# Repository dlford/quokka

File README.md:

## Moved to Codeberg

This project has migrated to [Codeberg](https://codeberg.org/dlford/quokka).

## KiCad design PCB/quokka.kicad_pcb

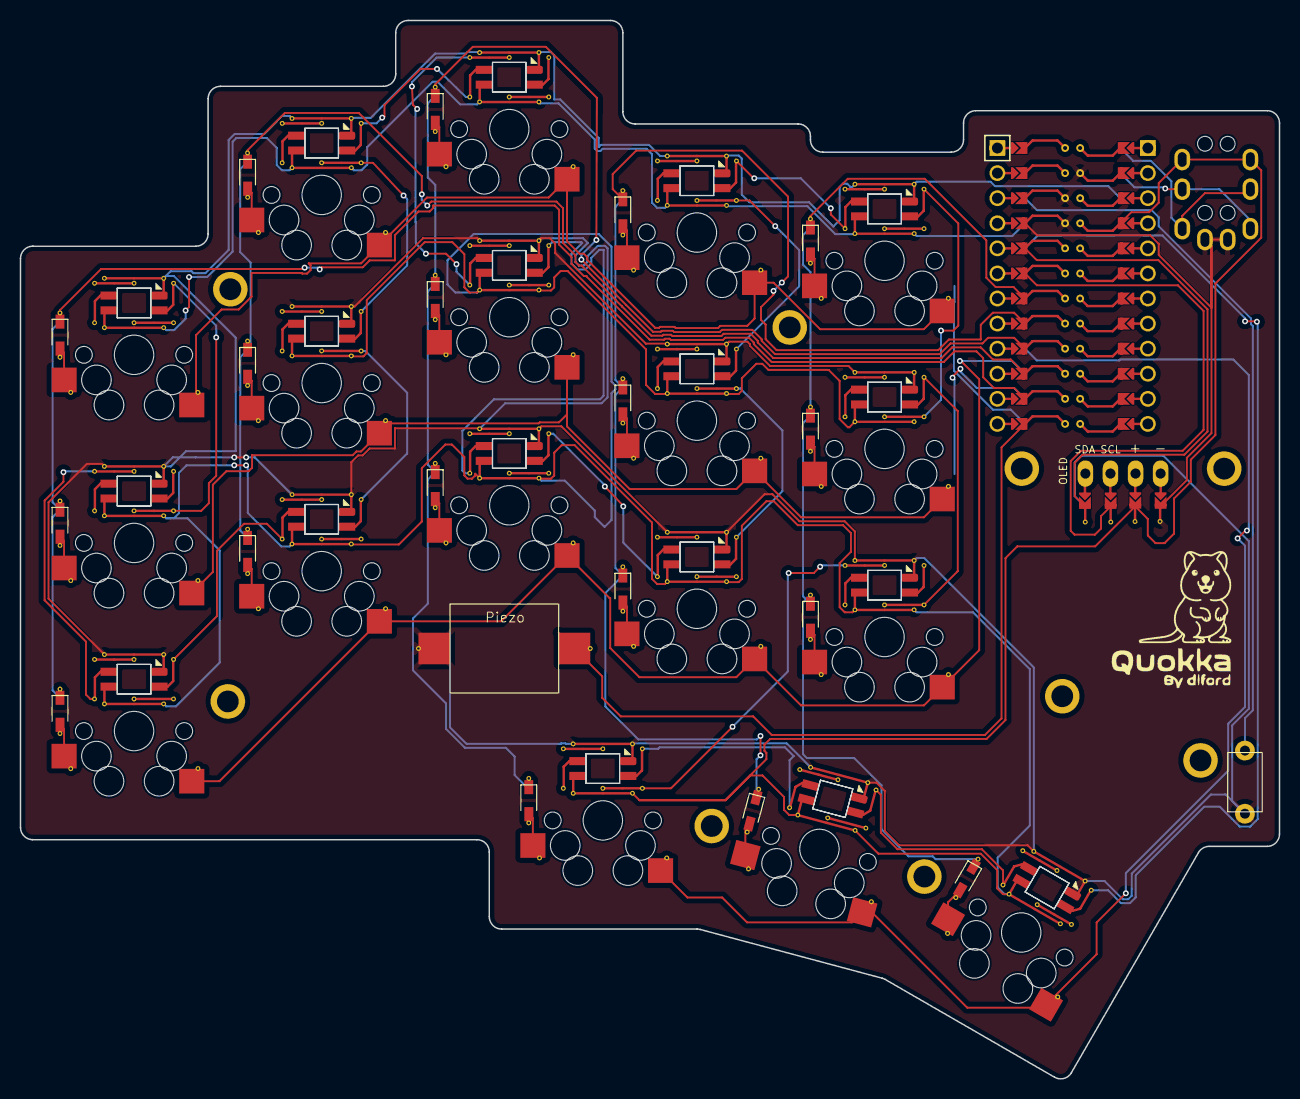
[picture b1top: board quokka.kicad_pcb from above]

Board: 2 copper layers, 127.5 x 107.2 mm, 20 parts (0 on the bottom side), 8 nets.

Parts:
MCU1: ProMicro
S1, S2, S3, S4, S5, S6, S7, S8, S9, S10, S11, S12, S13, S14, S15, S16, S17, S18: MX
TRRS1: TRRS-PJ-320A-dual

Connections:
GND: MCU1.2, MCU1.21, MCU1.22, TRRS1.1
P0: MCU1.23, TRRS1.3
P1: MCU1.24, TRRS1.2
P10: MCU1.12, S3.1, S6.1, S9.1, S12.1, S15.1
P14: MCU1.10, S1.1, S4.1, S7.1, S10.1, S13.1
P15: MCU1.9, S16.1, S17.1, S18.1
P16: MCU1.11, S2.1, S5.1, S8.1, S11.1, S14.1
VCC: MCU1.4, TRRS1.4

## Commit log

2023-04-13 start on quokka
2023-04-13 add diodes
2023-04-13 add reset button
2023-04-13 progress on routing
2023-04-13 matrix routed
2023-04-13 add leds
2023-04-14 add piezo
2023-04-14 add oled
2023-04-14 add vias for piezo and leds
2023-04-14 remove tht on diodes, add vias
2023-04-14 add din/dout led vias
2023-04-14 rotate switches
2023-04-14 moving vias to footprints
2023-04-14 replace diodes with 0805 footprint
2023-04-15 pre-via/trace leds, piezo, diodes
2023-04-15 pre-via mx switches
2023-04-15 fix pinout collision, start on reversable oled
2023-04-15 make oled reversable
2023-04-15 progress on case design
2023-04-15 swap out / shuffle TRRS and reset switch
2023-04-15 fine tune screw holes, oled cover
2023-04-15 relocate piezo
2023-04-15 add oled mounting holes
2023-04-15 re-organize files, eject from ergogen
2023-04-15 clean up
2023-04-16 add pcb logo
2023-04-16 routing PCB
2023-04-16 finished tracing PCB
2023-04-16 clean up traces
2023-04-16 remove oled outline
2023-04-16 test PCBs in production
2023-04-18 start on 3d printed case
2023-04-18 3d printed case WIP
2023-04-19 add polarity markers to silkscreen layers for piezo
2023-05-02 fix: rgb matrix traces overlapping in two places
2023-05-05 reshape case and PCB
2023-05-05 re-wire TRRS jacks for full duplex serial connection
2023-05-05 add ground planes to PCB
2023-05-05 add silk labels to PCB
2023-05-05 fix: bottom plate wrong dimensions
2023-05-11 update GND zone on PCB to cover all empty space
2023-05-15 update build photo
2023-05-17 progress on plate case
2023-05-17 update build guide
2023-05-18 add qmk firmware folder
2023-05-18 Revert "add qmk firmware folder"
    This reverts commit 209d2ae0e0154010866d885127cce3188c7cf81b.
2023-06-10 adjust reference with a designator
    Autorouting with Freerouting in KiCad is giving an error message about too many REF** or empty reference names. Therefore, I adjusted the references and added a designator to the parameters.
2023-06-10 remove tstamp from adjusted footprints
2026-03-08 moved to codeberg
